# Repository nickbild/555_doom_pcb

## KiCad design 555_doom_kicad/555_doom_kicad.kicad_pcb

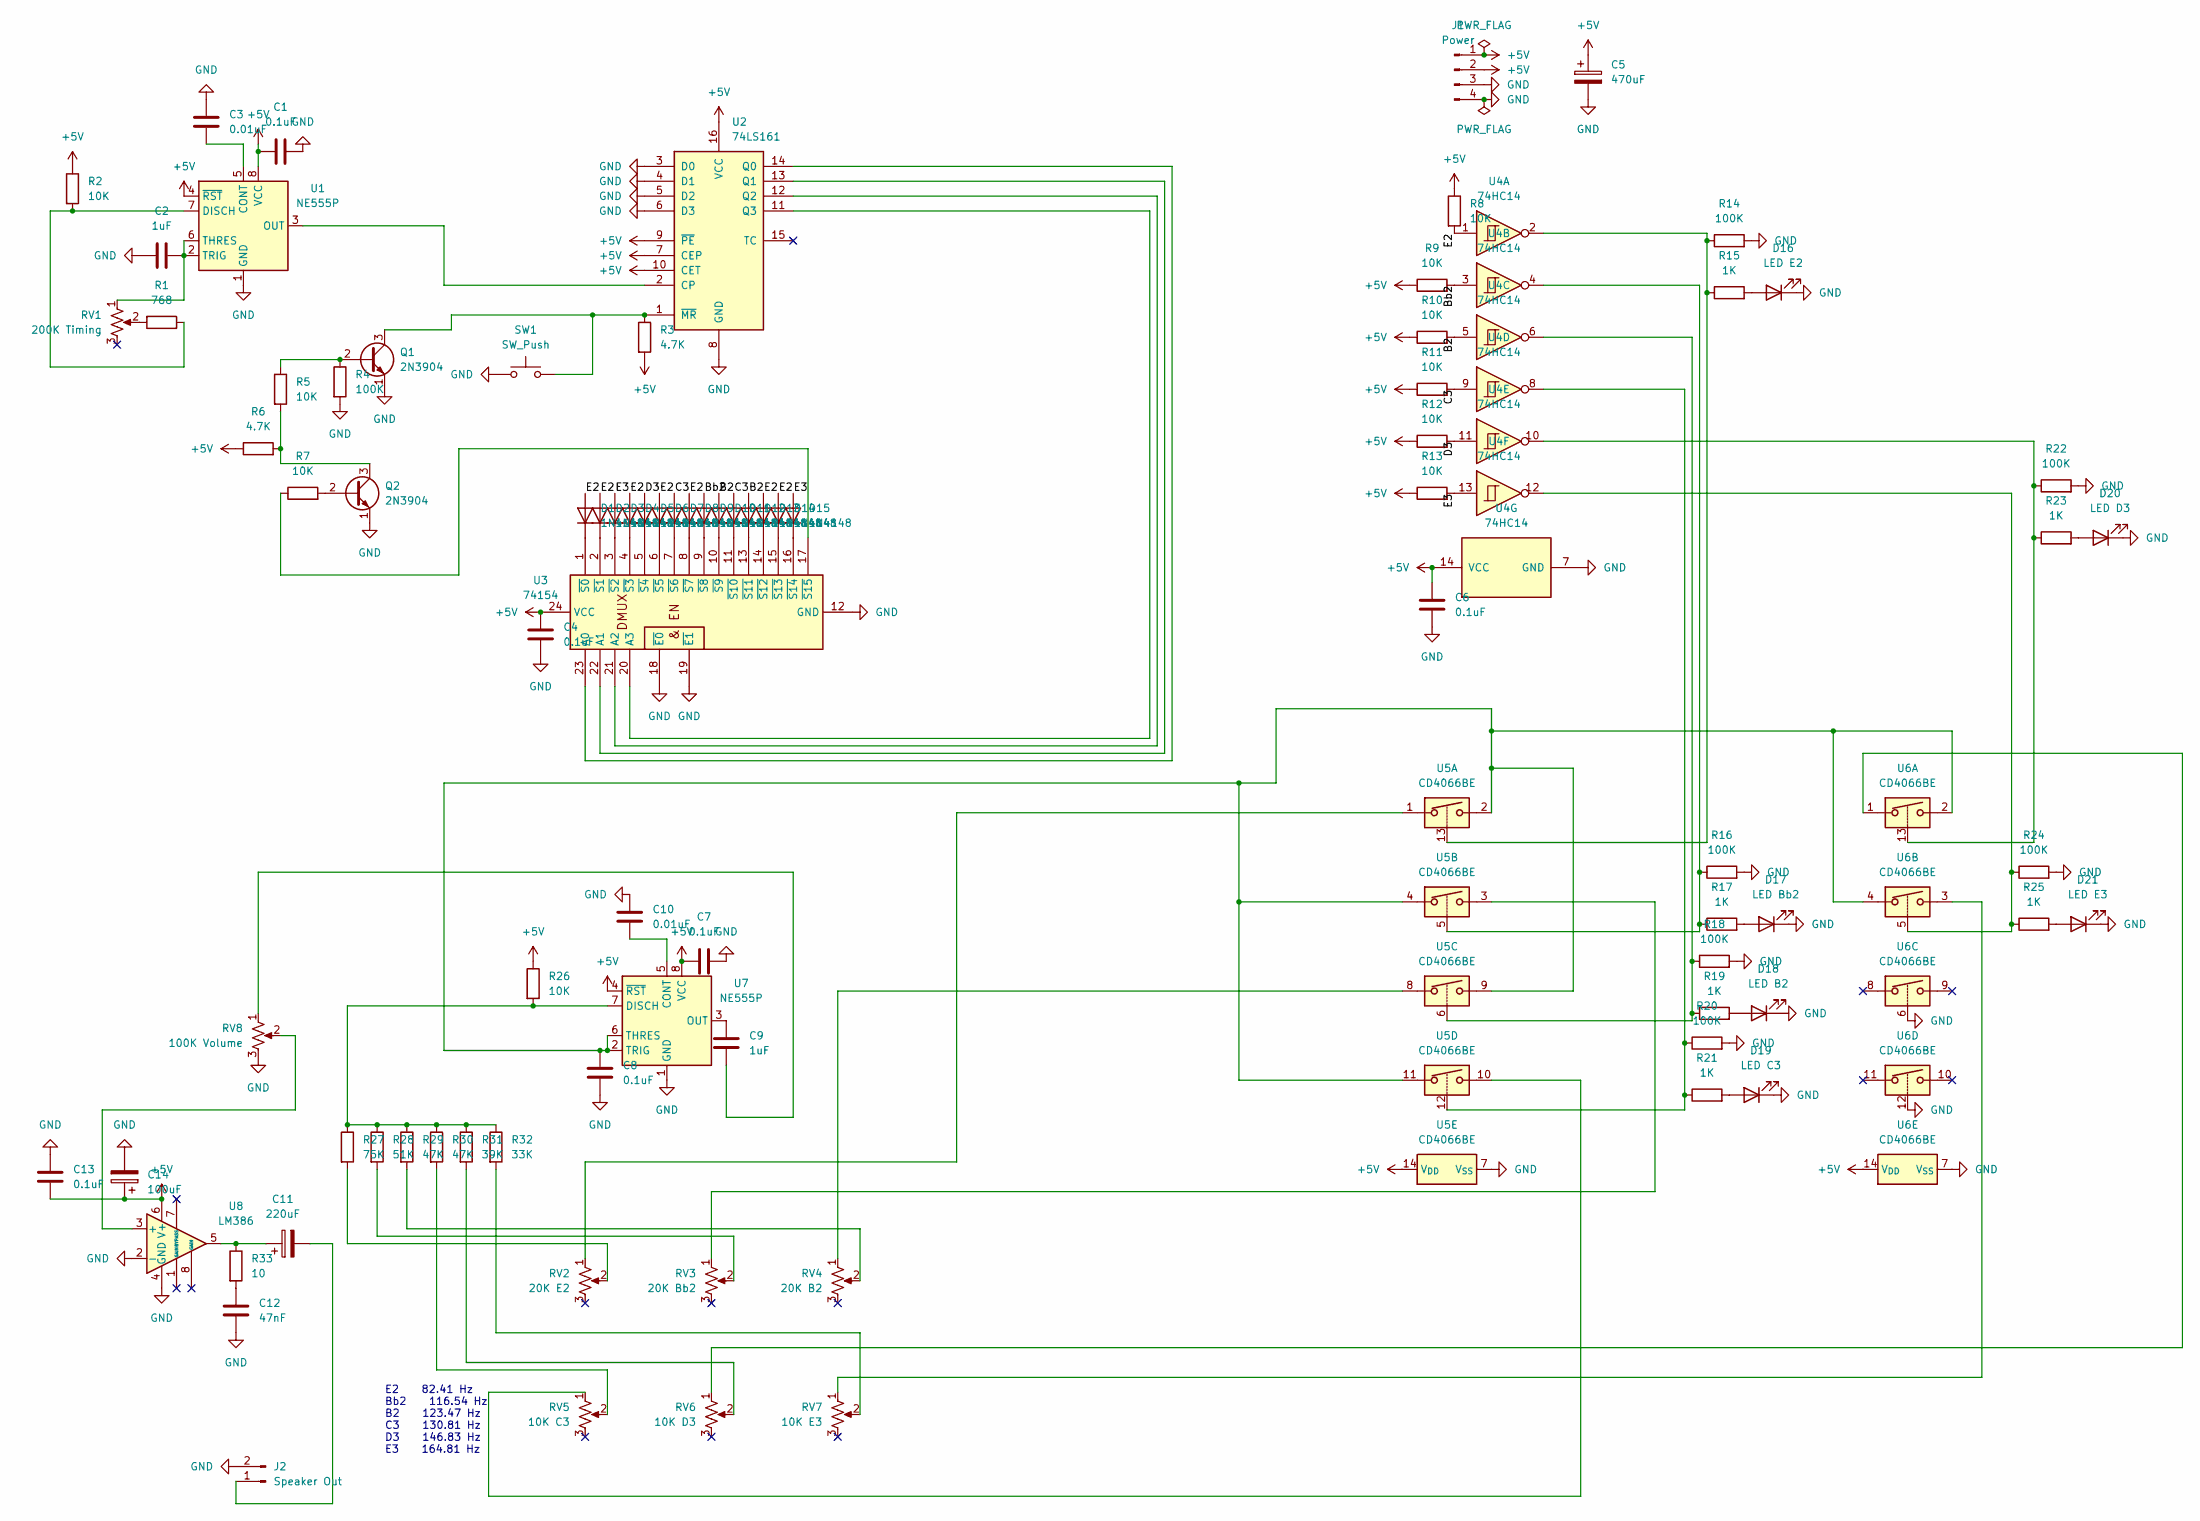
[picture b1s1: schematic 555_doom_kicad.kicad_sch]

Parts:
C1, C4, C6, C7, C8, C13: 0.1uF; C_Disc_D4.7mm_W2.5mm_P5.00mm
C2, C9: 1uF; C_Disc_D4.7mm_W2.5mm_P5.00mm
C3, C10: 0.01uF; C_Disc_D4.7mm_W2.5mm_P5.00mm
C5: 470uF; CP_Radial_D8.0mm_P2.50mm
C11: 220uF; CP_Radial_D5.0mm_P2.50mm
C12: 47nF; C_Disc_D4.7mm_W2.5mm_P5.00mm
C14: 100uF; CP_Radial_D5.0mm_P2.50mm
D1, D2, D3, D4, D5, D6, D7, D8, D9, D10, D11, D12, D13, D14, D15: 1N4148; D_T-1_P5.08mm_Horizontal
D16: LED E2; LED_D5.0mm
D17: LED Bb2; LED_D5.0mm
D18: LED B2; LED_D5.0mm
D19: LED C3; LED_D5.0mm
D20: LED D3; LED_D5.0mm
D21: LED E3; LED_D5.0mm
J1: Power; PinHeader_1x04_P2.54mm_Vertical
J2: Speaker Out; PinHeader_1x02_P2.54mm_Vertical
Q1, Q2: 2N3904; TO-92_Inline_Wide
R1: 768; R_Axial_DIN0207_L6.3mm_D2.5mm_P7.62mm_Horizontal
R2, R5, R7, R8, R9, R10, R11, R12, R13, R26: 10K; R_Axial_DIN0207_L6.3mm_D2.5mm_P7.62mm_Horizontal
R3, R6: 4.7K; R_Axial_DIN0207_L6.3mm_D2.5mm_P7.62mm_Horizontal
R4, R14, R16, R18, R20, R22, R24: 100K; R_Axial_DIN0207_L6.3mm_D2.5mm_P7.62mm_Horizontal
R15, R17, R19, R21, R23, R25: 1K; R_Axial_DIN0207_L6.3mm_D2.5mm_P7.62mm_Horizontal
R27: 75K; R_Axial_DIN0207_L6.3mm_D2.5mm_P7.62mm_Horizontal
R28: 51K; R_Axial_DIN0207_L6.3mm_D2.5mm_P7.62mm_Horizontal
R29, R30: 47K; R_Axial_DIN0207_L6.3mm_D2.5mm_P7.62mm_Horizontal
R31: 39K; R_Axial_DIN0207_L6.3mm_D2.5mm_P7.62mm_Horizontal
R32: 33K; R_Axial_DIN0207_L6.3mm_D2.5mm_P7.62mm_Horizontal
R33: 10; R_Axial_DIN0207_L6.3mm_D2.5mm_P7.62mm_Horizontal
RV1: 200K Timing; Potentiometer_ACP_CA9-H5_Horizontal
RV2: 20K E2; Potentiometer_ACP_CA9-H5_Horizontal
RV3: 20K Bb2; Potentiometer_ACP_CA9-H5_Horizontal
RV4: 20K B2; Potentiometer_ACP_CA9-H5_Horizontal
RV5: 10K C3; Potentiometer_ACP_CA9-H5_Horizontal
RV6: 10K D3; Potentiometer_ACP_CA9-H5_Horizontal
RV7: 10K E3; Potentiometer_ACP_CA9-H5_Horizontal
RV8: 100K Volume; Potentiometer_ACP_CA9-H5_Horizontal
SW1: SW_Push; SW_PUSH_6mm_H7.3mm
U1, U7: NE555P; DIP-8_W7.62mm
U2: 74LS161; DIP-16_W7.62mm
U3: 74154; DIP-24_W15.24mm
U4: 74HC14; DIP-14_W7.62mm
U5, U6: CD4066BE; DIP-14_W7.62mm
U8: LM386; DIP-8_W7.62mm

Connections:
+5V: C1.1, C4.1, C5.1, C6.1, C7.1, C13.2, C14.1, J1.1, J1.2, R2.1, R3.2, R6.1, R8.1, R9.1, R10.1, R11.1, R12.1, R13.1, R26.1, U1.4 (~RST), U1.8 (VCC), U2.7 (CEP), U2.9 (~PE), U2.10 (CET), U2.16 (VCC), U3.24 (VCC), U4.14 (VCC), U5.14 (V_{DD}), U6.14 (V_{DD}), U7.4 (~RST), U7.8 (VCC), U8.6 (V+)
/B2: D10.2 (A), D12.2 (A), R10.2, U4.5
/Bb2: D9.2 (A), R9.2, U4.3
/C3: D7.2 (A), D11.2 (A), R11.2, U4.9
/D3: D5.2 (A), R12.2, U4.11
/E2: D1.2 (A), D2.2 (A), D4.2 (A), D6.2 (A), D8.2 (A), D13.2 (A), D14.2 (A), R8.2, U4.1
/E3: D3.2 (A), D15.2 (A), R13.2, U4.13
GND: C1.2, C2.2, C3.1, C4.2, C5.2, C6.2, C7.2, C8.2, C10.1, C12.2, C13.1, C14.2, D16.1 (K), D17.1 (K), D18.1 (K), D19.1 (K), D20.1 (K), D21.1 (K), J1.3, J1.4, J2.2, Q1.1 (E), Q2.1 (E), R4.2, R14.2, R16.2, R18.2, R20.2, R22.2, R24.2, RV8.3, SW1.1, U1.1 (GND), U2.3 (D0), U2.4 (D1), U2.5 (D2), U2.6 (D3), U2.8 (GND), U3.12 (GND), U3.18 (~E0), U3.19 (~E1), U4.7 (GND), U5.7 (V_{SS}), U6.6, U6.7 (V_{SS}), U6.12, U7.1 (GND), U8.2 (-), U8.4 (GND)
unnamed: C9.2, RV8.1
unnamed: C11.1, R33.1, U8.5
unnamed: C12.1, R33.2
unnamed: D1.1 (K), U3.1 (~S0)
unnamed: D2.1 (K), U3.2 (~S1)
unnamed: D3.1 (K), U3.3 (~S2)
unnamed: D4.1 (K), U3.4 (~S3)
unnamed: D5.1 (K), U3.5 (~S4)
unnamed: D6.1 (K), U3.6 (~S5)
unnamed: D7.1 (K), U3.7 (~S6)
unnamed: D8.1 (K), U3.8 (~S7)
unnamed: D9.1 (K), U3.9 (~S8)
unnamed: D10.1 (K), U3.10 (~S9)
unnamed: D11.1 (K), U3.11 (~S10)
unnamed: D12.1 (K), U3.13 (~S11)
unnamed: D13.1 (K), U3.14 (~S12)
unnamed: D14.1 (K), U3.15 (~S13)
unnamed: D15.1 (K), U3.16 (~S14)
unnamed: D16.2 (A), R15.2
unnamed: D17.2 (A), R17.2
unnamed: D18.2 (A), R19.2
unnamed: D19.2 (A), R21.2
unnamed: D20.2 (A), R23.2
unnamed: D21.2 (A), R25.2
unnamed: C11.2, J2.1
unnamed: Q1.2 (B), R4.1, R5.1
unnamed: Q1.3 (C), R3.1, SW1.2, U2.1 (~MR)
unnamed: Q2.2 (B), R7.2
unnamed: Q2.3 (C), R5.2, R6.2
unnamed: R1.2, RV1.2
unnamed: R14.1, R15.1, U4.2, U5.13
unnamed: R16.1, R17.1, U4.4, U5.5
unnamed: R18.1, R19.1, U4.6, U5.6
unnamed: R20.1, R21.1, U4.8, U5.12
unnamed: R22.1, R23.1, U4.10, U6.13
unnamed: R24.1, R25.1, U4.12, U6.5
unnamed: R27.2, RV2.2
unnamed: R28.2, RV3.2
unnamed: R29.2, RV4.2
unnamed: R30.2, RV5.2
unnamed: R31.2, RV6.2
unnamed: R32.2, RV7.2
unnamed: RV2.1, U5.1
unnamed: RV3.1, U5.3
unnamed: RV4.1, U5.8
unnamed: RV5.1, U5.10
unnamed: RV6.1, U6.1
unnamed: RV7.1, U6.3
unnamed: C3.2, U1.5 (CONT)
unnamed: R1.1, R2.2, U1.7 (DISCH)
unnamed: U1.3 (OUT), U2.2 (CP)
unnamed: C2.1, RV1.1, U1.2 (TRIG), U1.6 (THRES)
unnamed: U2.14 (Q0), U3.23 (A0)
unnamed: U2.13 (Q1), U3.22 (A1)
unnamed: U2.12 (Q2), U3.21 (A2)
unnamed: U2.11 (Q3), U3.20 (A3)
unnamed: R7.1, U3.17 (~S15)
unnamed: C10.2, U7.5 (CONT)
unnamed: R26.2, R27.1, R28.1, R29.1, R30.1, R31.1, R32.1, U7.7 (DISCH)
unnamed: C9.1, U7.3 (OUT)
unnamed: C8.1, U5.2, U5.4, U5.9, U5.11, U6.2, U6.4, U7.2 (TRIG), U7.6 (THRES)
unnamed: RV8.2, U8.3 (+)

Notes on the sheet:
E2 82.41 Hz Bb2 116.54 Hz B2 123.47 Hz C3 130.81 Hz D3 146.83 Hz E3 164.81 Hz

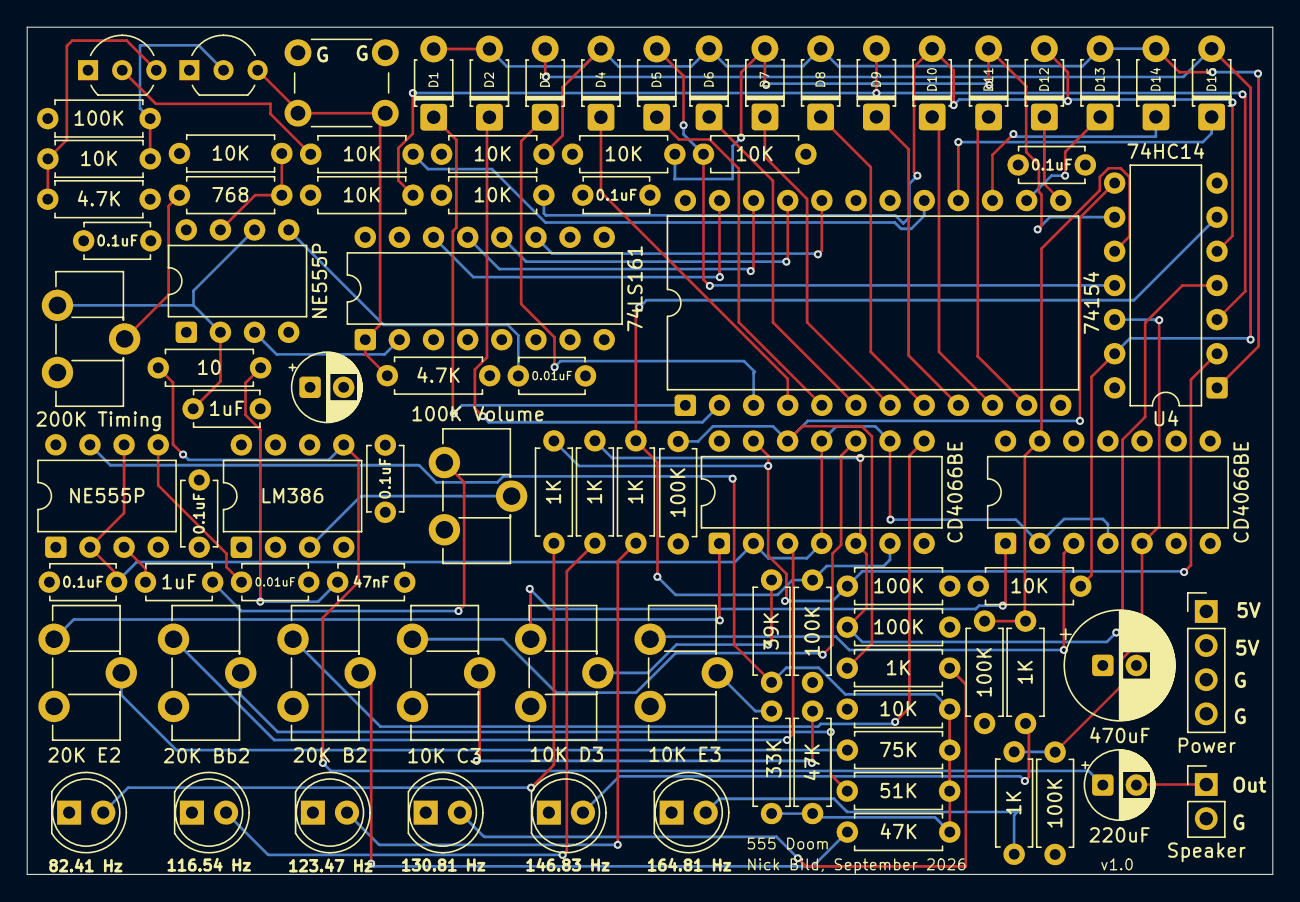
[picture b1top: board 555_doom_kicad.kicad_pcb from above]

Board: 4 copper layers, 92.7 x 63.0 mm, 89 parts (0 on the bottom side), 70 nets.
